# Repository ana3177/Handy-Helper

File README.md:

# Handy-Helper
A visual timer for washing hands

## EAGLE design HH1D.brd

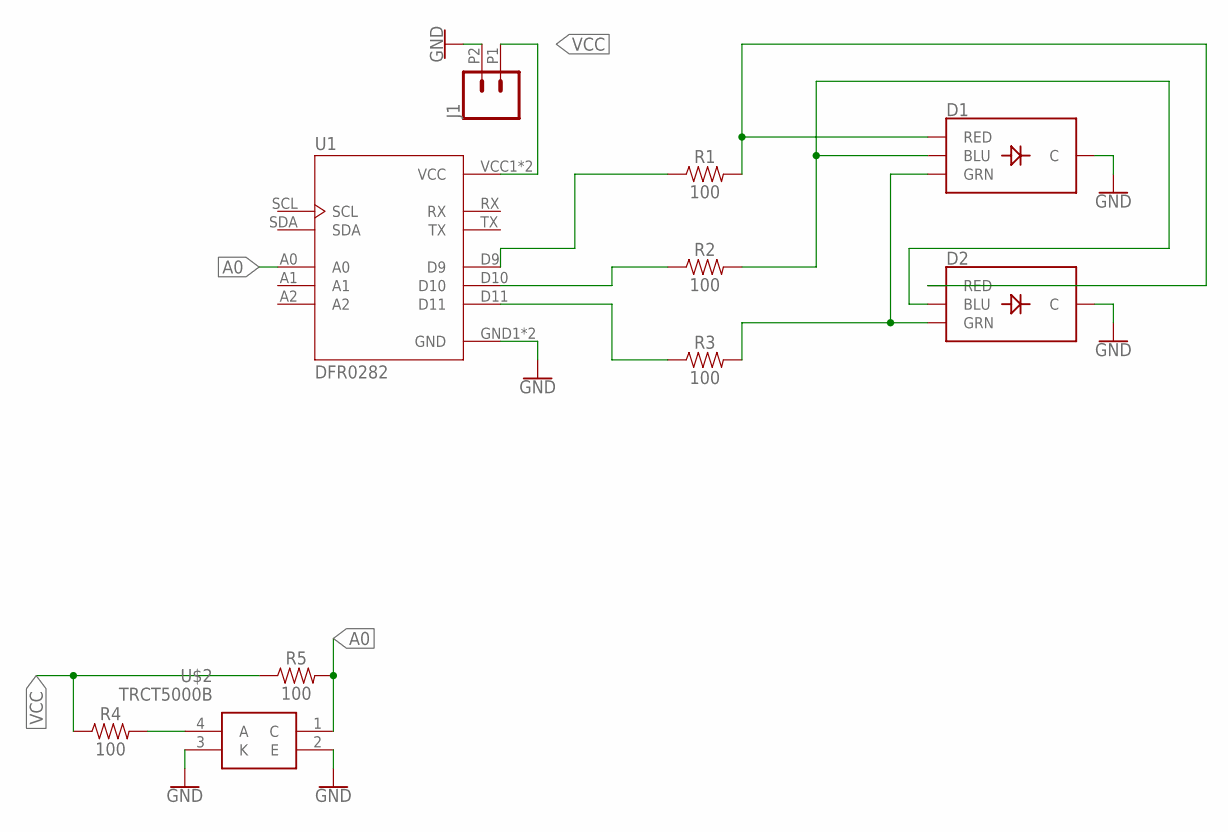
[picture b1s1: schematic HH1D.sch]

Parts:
D1, D2: LED-RGB-CCPIRANHA; LED_PIRANHA_5MM
J1: CONN_022.54MM_SCREWTERM; 1X02_2.54_SCREWTERM
R1, R2, R3, R4, R5: 100; AXIAL-0.3
U1: DFR0282; MODULE_DFR0282
U$2: TRCT5000B

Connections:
A0: R5.P$2 (2), U1.A0, U$2.1 (C)
GND: D1.- (C), D2.- (C), J1.P2 (2), U1.GND1 (GND), U1.GND2 (GND), U$2.2 (E), U$2.3 (K)
unnamed: D1.R (RED), D2.R (RED), R1.P$2 (2)
unnamed: D1.B (BLU), D2.B (BLU), R2.P$2 (2)
unnamed: D1.G (GRN), D2.G (GRN), R3.P$2 (2)
unnamed: R4.P$2 (2), U$2.4 (A)
unnamed: R1.P$1 (1), U1.D9
unnamed: R2.P$1 (1), U1.D10
unnamed: R3.P$1 (1), U1.D11
VCC: J1.P1 (1), R4.P$1 (1), R5.P$1 (1), U1.VCC1 (VCC), U1.VCC2 (VCC)

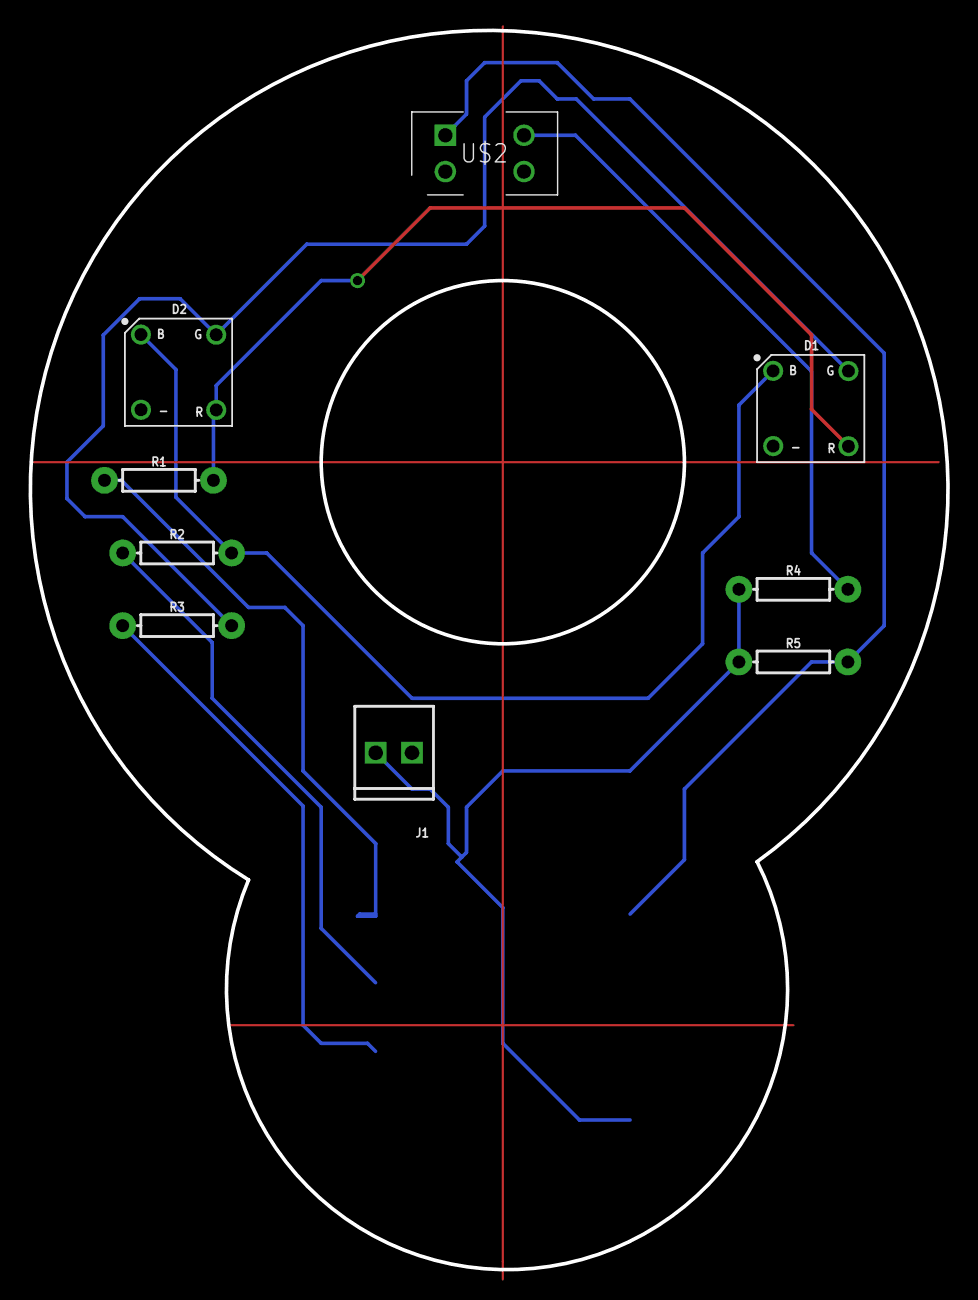
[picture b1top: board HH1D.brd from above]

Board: 2 copper layers, 64.2 x 86.7 mm, 10 parts (1 on the bottom side), 10 nets.

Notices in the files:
parts and their libraries:
SparkFun-LED: Licensing: Creative Commons ShareAlike 4.0 International - https://creativecommons.org/licenses/by-sa/4.0
